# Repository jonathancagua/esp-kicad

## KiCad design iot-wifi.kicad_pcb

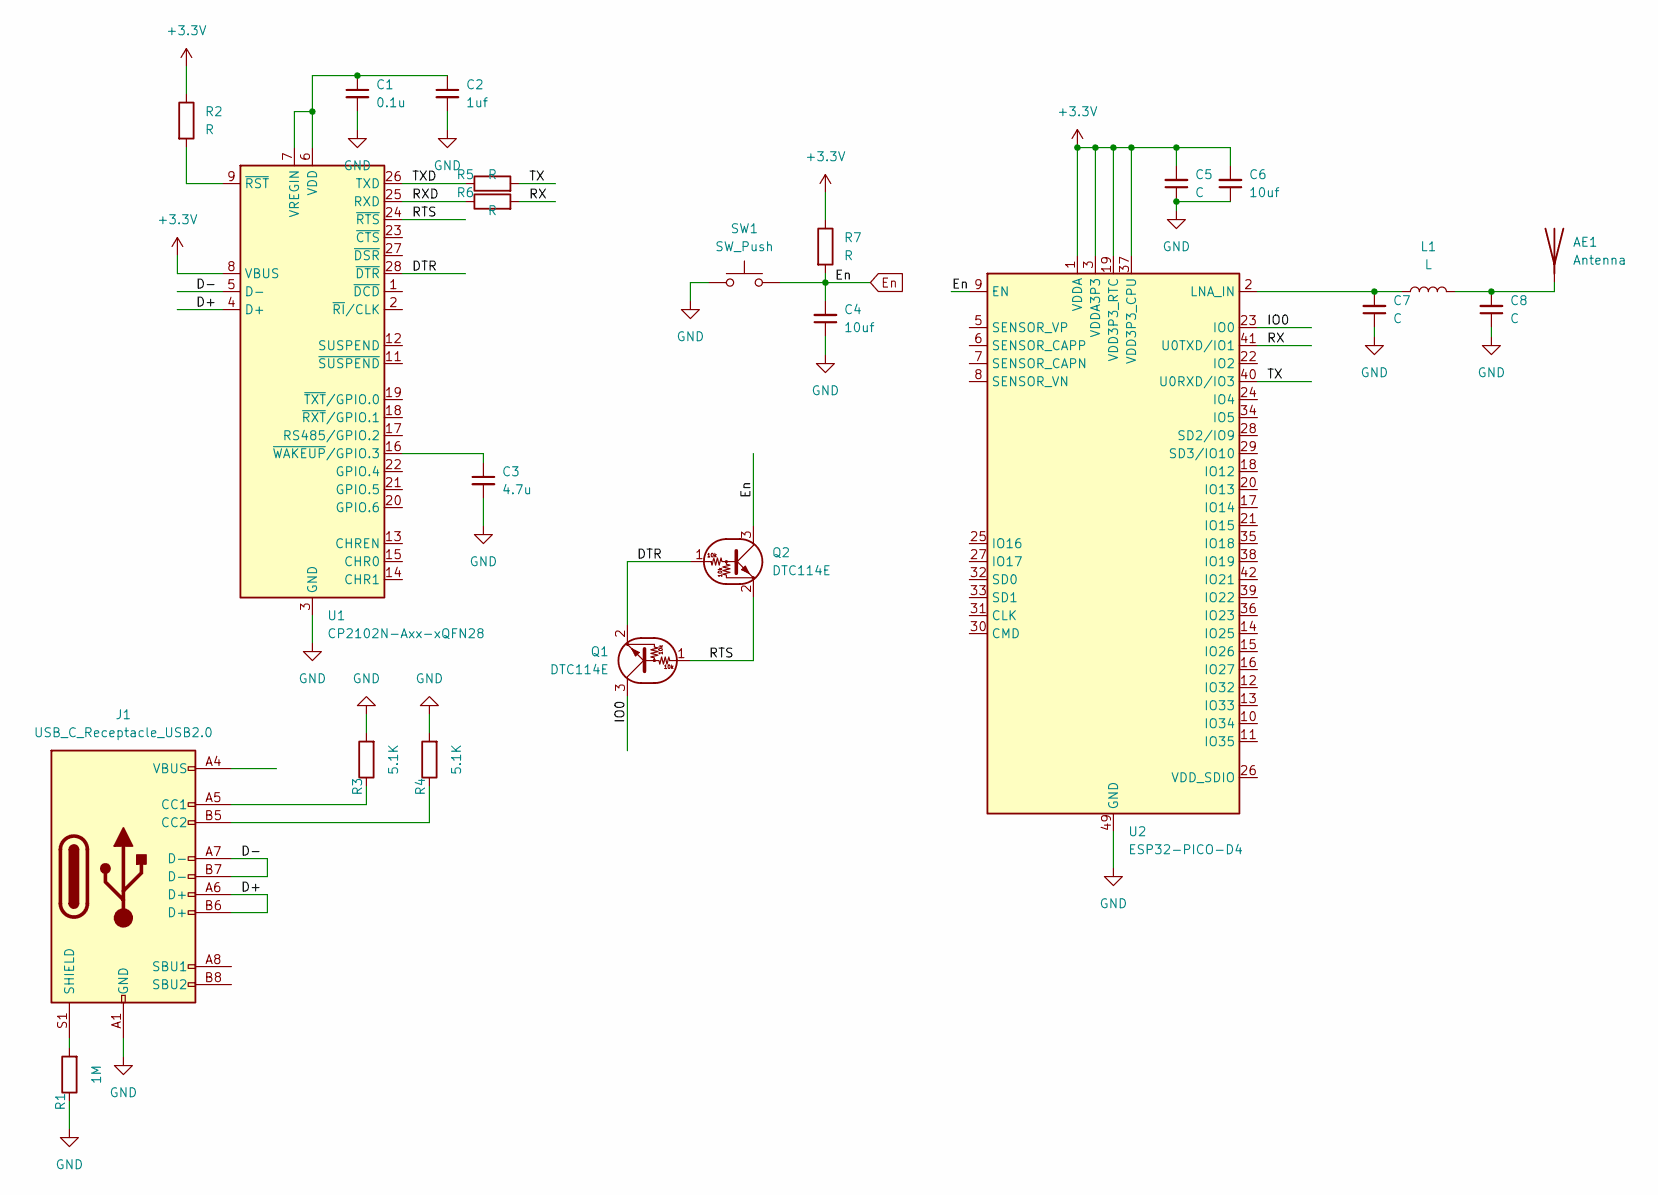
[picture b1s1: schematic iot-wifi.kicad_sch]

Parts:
AE1: Antenna
C1: 0.1u; C_0402_1005Metric_Pad0.74x0.62mm_HandSolder
C2: 1uf; C_0402_1005Metric_Pad0.74x0.62mm_HandSolder
C3: 4.7u; C_0402_1005Metric_Pad0.74x0.62mm_HandSolder
C4, C6: 10uf; C_0402_1005Metric_Pad0.74x0.62mm_HandSolder
C5, C7, C8: C; C_0402_1005Metric_Pad0.74x0.62mm_HandSolder
J1: USB_C_Receptacle_USB2.0; USB_C_Receptacle_JAE_DX07S016JA1R1500
L1: L; L_01005_0402Metric_Pad0.57x0.30mm_HandSolder
Q1, Q2: DTC114E; SOT-416
R1: 1M; R_0201_0603Metric_Pad0.64x0.40mm_HandSolder
R2, R5, R6, R7: R; R_0402_1005Metric_Pad0.72x0.64mm_HandSolder
R3, R4: 5.1K; R_0402_1005Metric_Pad0.72x0.64mm_HandSolder
SW1: SW_Push; SW_SPST_B3U-1000P
U1: CP2102N-Axx-xQFN28; QFN-28-1EP_5x5mm_P0.5mm_EP3.35x3.35mm
U2: ESP32-PICO-D4; QFN-48-1EP_7x7mm_P0.5mm_EP5.3x5.3mm_ThermalVias

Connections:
+3V3: C5.2, C6.2, R2.1, R7.1, U1.8 (VBUS), U2.1 (VDDA), U2.3 (VDDA3P3), U2.4 (VDDA3P3), U2.19 (VDD3P3_RTC), U2.37 (VDD3P3_CPU), U2.43 (VDDA), U2.46 (VDDA)
/D+: J1.A6 (D+), J1.B6 (D+), U1.4 (D+)
/D-: J1.A7 (D-), J1.B7 (D-), U1.5 (D-)
/DTR: Q1.2 (E), Q2.1 (B), U1.28 (~DTR)
/IO0: Q1.3 (C), U2.23 (IO0)
/RTS: Q1.1 (B), Q2.2 (E), U1.24 (~RTS)
/RX: R6.2, U2.41 (U0TXD/IO1)
/RXD: R6.1, U1.25 (RXD)
/TX: R5.2, U2.40 (U0RXD/IO3)
/TXD: R5.1, U1.26 (TXD)
En: C4.2, Q2.3 (C), R7.2, SW1.2, U2.9 (EN)
GND: C1.2, C2.2, C3.2, C4.1, C5.1, C6.1, C7.1, C8.1, J1.A1 (GND), J1.A12 (GND), J1.B1 (GND), J1.B12 (GND), R1.1, R3.2, R4.2, SW1.1, U1.3 (GND), U1.29 (GND), U2.49 (GND)
unnamed: AE1.1, C8.2, L1.2
unnamed: C1.1, C2.1, U1.6 (VDD), U1.7 (VREGIN)
unnamed: C3.1, U1.16 (~WAKEUP/GPIO.3)
unnamed: C7.2, L1.1, U2.2 (LNA_IN)
unnamed: J1.A4 (VBUS), J1.A9 (VBUS), J1.B4 (VBUS), J1.B9 (VBUS)
unnamed: J1.A5 (CC1), R3.1
unnamed: J1.B5 (CC2), R4.1
unnamed: J1.S1 (SHIELD), R1.2
unnamed: R2.2, U1.9 (~RST)

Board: 2 copper layers, 22 parts (0 on the bottom side), 21 nets, no tracks yet.

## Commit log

2022-02-20 ADD: basic schematic
2022-02-20 FIX: error data
2022-06-25 ADD: esp32
